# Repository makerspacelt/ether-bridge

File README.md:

---

Ether-bridge

NOTE: This is only a prototype now, so things might not work, and everything might change 

This hardware is meant as an Ethernet upgrade for devices that only support
I2C/UART/RS485/CAN communications. This should be used with a device-specific
firmware that exposes SCPI commands for all functions of a particular device.

Basic target features:

* Ethernet connection
* PoE .af 12w
* CAN
* RS-485
* i2c/UART
* 1x GPIO
* LXI/SCPI support via raw TCP
* Compatibility with ESPHome and Home Assistant

Dev NOTE: before commit, run `./kibot.sh` to regenerate documentation, bom, gerbers and other assets.

* [schematics.pdf](gen/schematics.pdf)
* [pcb.pdf with dimensions](gen/pcb.pdf)
* [ibom.html](gen/single/ibom.html)

---

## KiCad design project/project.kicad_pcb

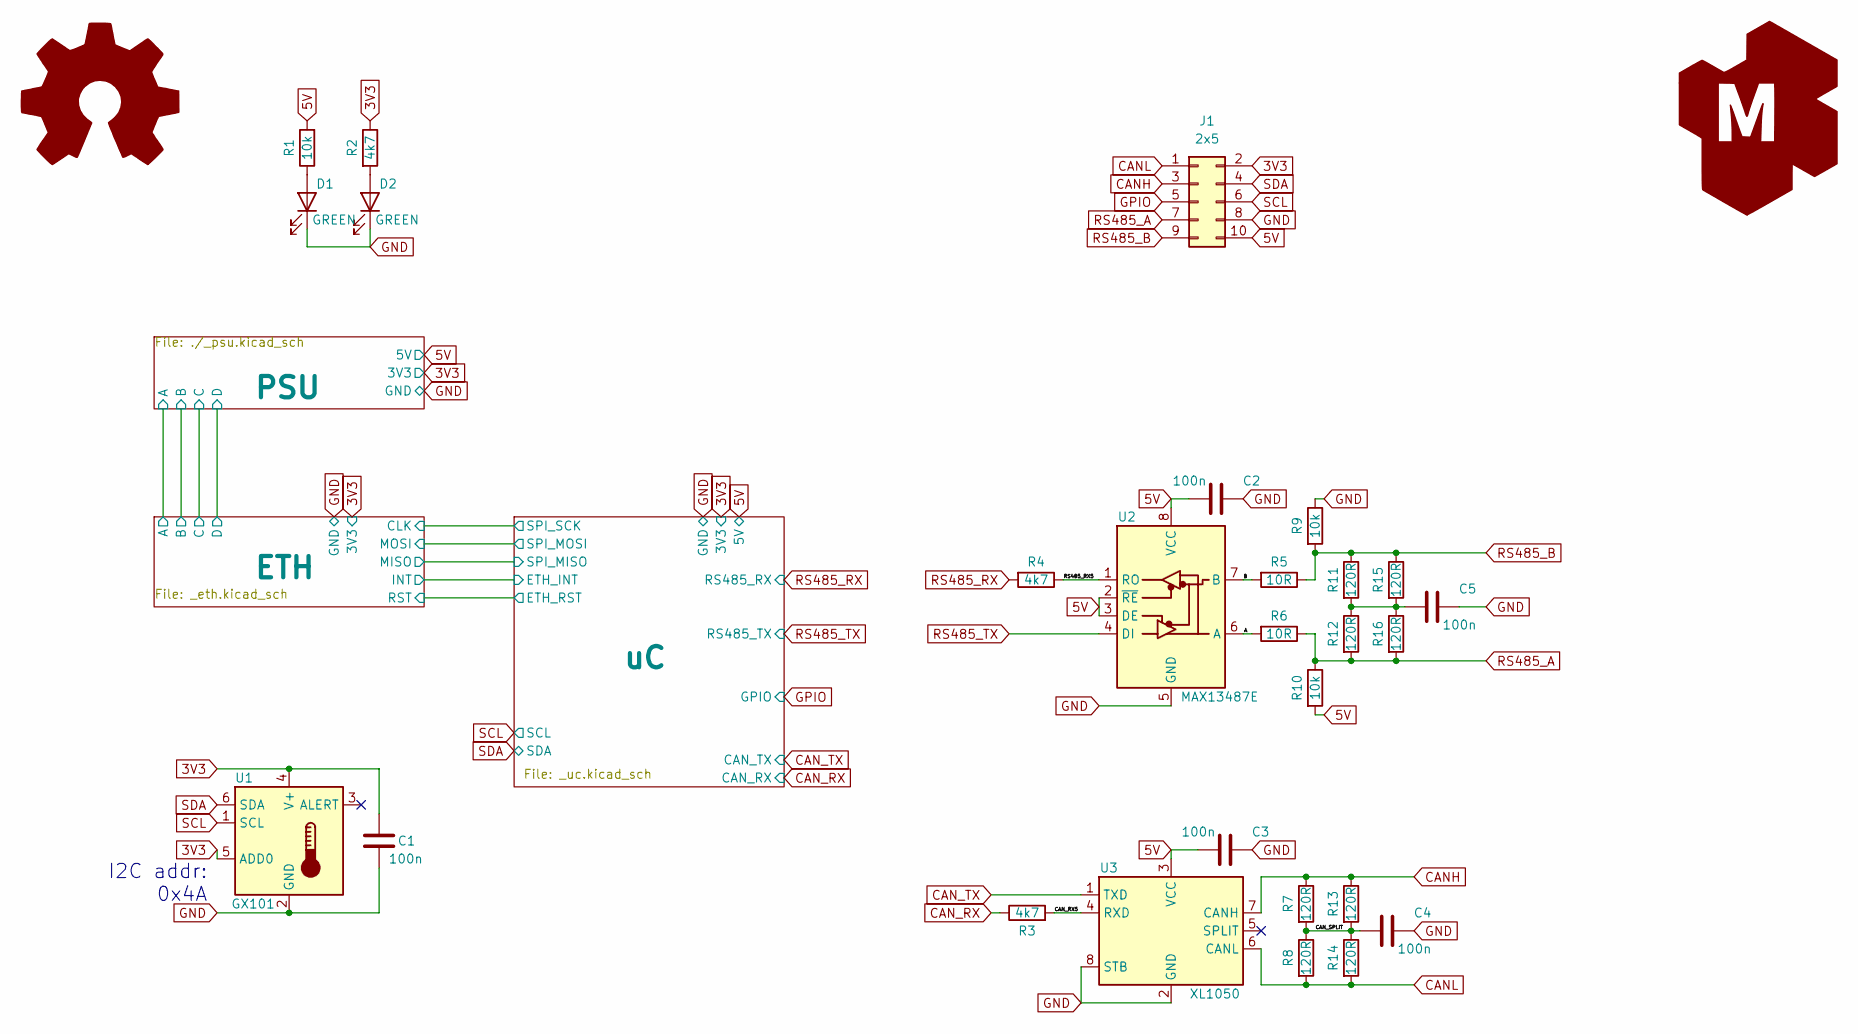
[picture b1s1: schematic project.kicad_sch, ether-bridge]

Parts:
C1, C2, C3, C4, C5: 100n; C_0402_1005Metric_Pad0.74x0.62mm_HandSolder; jlc-part-type B+
D1, D2: GREEN; LED_0805_2012Metric_Pad1.15x1.40mm_HandSolder; jlc-part-type B+
G1: Logo_Open_Hardware_Large; OSHW-Symbol_6.7x6mm_SilkScreen
G2: LOGO_KMS; logo_kms_small_silkscreen
J1: 2x5; PinHeader_2x05_P2.54mm_Vertical
R1, R9, R10: 10k; R_0402_1005Metric_Pad0.72x0.64mm_HandSolder; jlc-part-type B+
R2, R3, R4: 4k7; R_0402_1005Metric_Pad0.72x0.64mm_HandSolder; jlc-part-type B+
R5, R6: 10R; R_0402_1005Metric_Pad0.72x0.64mm_HandSolder; jlc-part-type B+
R7, R8, R11, R12, R13, R14, R15, R16: 120R; R_0402_1005Metric_Pad0.72x0.64mm_HandSolder; jlc-part-type B+
U1: GX101; SOT-23-6; jlc-part-type E+
U2: MAX13487E; SOIC-8_3.9x4.9mm_P1.27mm; jlc-part-type E+
U3: XL1050; SOIC-8_3.9x4.9mm_P1.27mm; jlc-part-type E+

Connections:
3V3: C1.1, J1.2, R2.1, U1.4 (V+), U1.5 (ADD0); also elsewhere on the board
5V: C2.1, C3.1, J1.10, R1.2, R10.2, U2.2 (~RE), U2.3 (DE), U2.8 (VCC), U3.3 (VCC); also elsewhere on the board
/A: R6.2, U2.6 (A)
/B: R5.2, U2.7 (B)
/CAN_RX5: R3.2, U3.4 (RXD)
/CAN_SPLIT: C4.1, R7.2, R8.1, R13.2, R14.1
/RS485_RX5: R4.1, U2.1 (RO)
CANH: J1.3, R7.1, R13.1, U3.7 (CANH)
CANL: J1.1, R8.2, R14.2, U3.6 (CANL)
CAN_RX: R3.1; also elsewhere on the board
CAN_TX: U3.1 (TXD); also elsewhere on the board
GND: C1.2, C2.2, C3.2, C4.2, C5.2, D1.1 (K), D2.1 (K), J1.8, R9.1, U1.2 (GND), U2.5 (GND), U3.2 (GND), U3.8 (STB); also elsewhere on the board
GPIO: J1.5; also elsewhere on the board
unnamed: C5.1, R11.2, R12.1, R15.2, R16.1
unnamed: D1.2 (A), R1.1
unnamed: D2.2 (A), R2.2
RS485_A: J1.7, R6.1, R10.1, R12.2, R16.2
RS485_B: J1.9, R5.1, R9.2, R11.1, R15.1
RS485_RX: R4.2; also elsewhere on the board
RS485_TX: U2.4 (DI); also elsewhere on the board
SCL: J1.6, U1.1 (SCL); also elsewhere on the board
SDA: J1.4, U1.6 (SDA); also elsewhere on the board

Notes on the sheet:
I2C addr: 0x4A

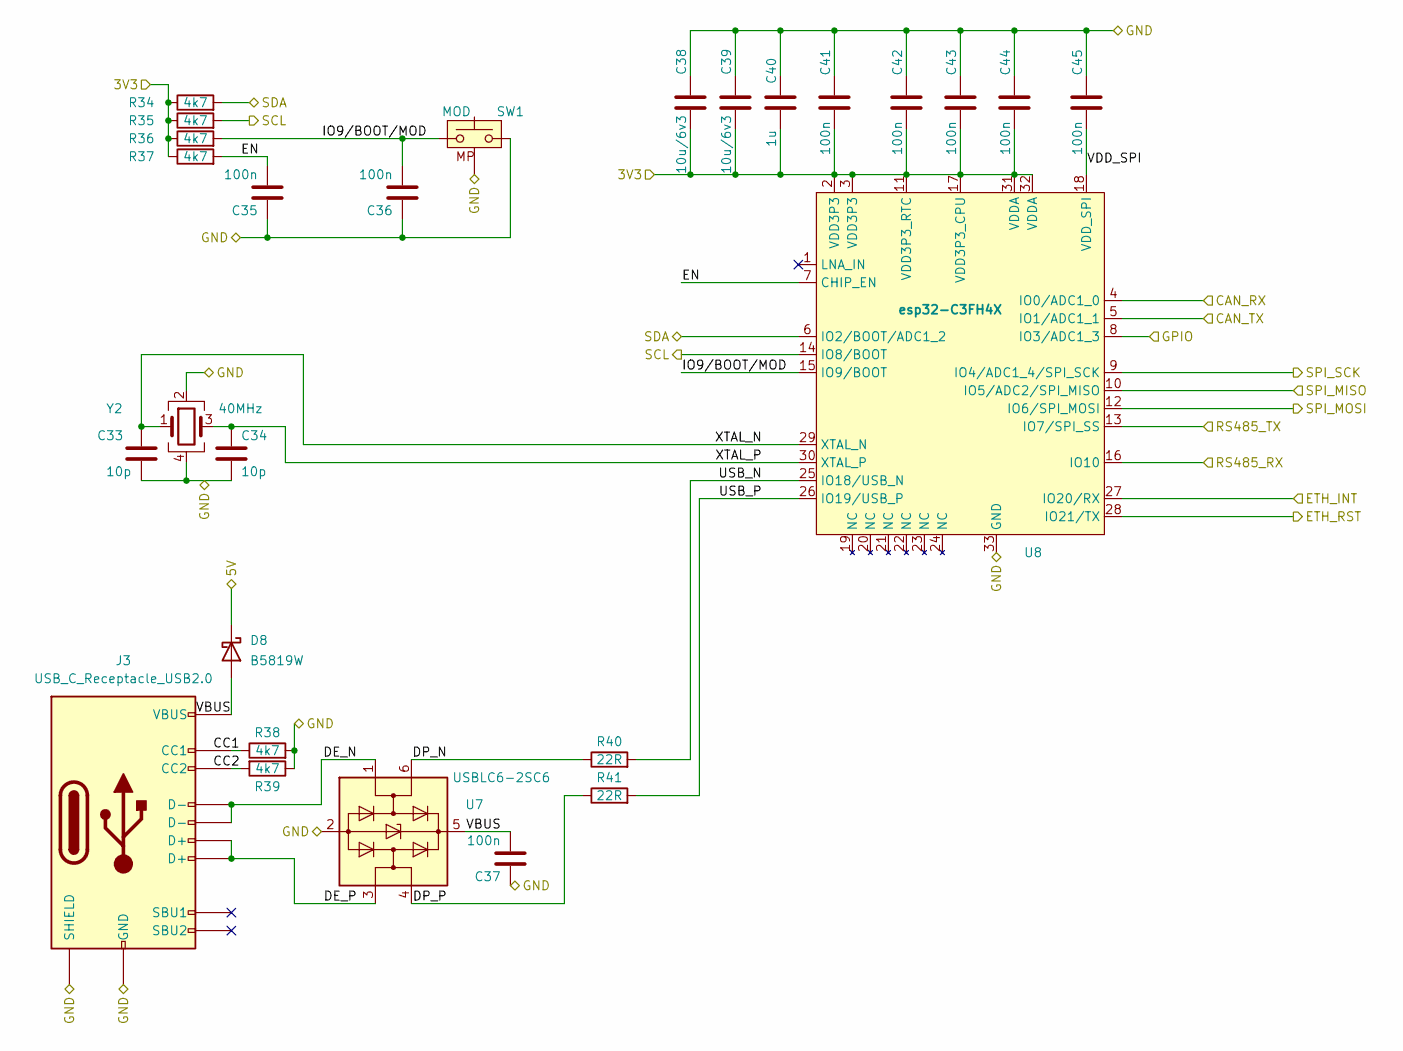
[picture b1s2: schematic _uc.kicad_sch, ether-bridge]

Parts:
C33, C34: 10p; C_0402_1005Metric; jlc-part-type ???
C35, C36, C37, C41, C42, C43, C44, C45: 100n; C_0402_1005Metric_Pad0.74x0.62mm_HandSolder; jlc-part-type B+
C38, C39: 10u/6v3; C_0402_1005Metric_Pad0.74x0.62mm_HandSolder; jlc-part-type B+
C40: 1u; C_0402_1005Metric_Pad0.74x0.62mm_HandSolder; jlc-part-type B+
D8: B5819W; D_SOD-123; jlc-part-type B+
J3: USB_C_Receptacle_USB2.0; USB_C_Receptacle_HRO_TYPE-C-31-M-12; jlc-part-type E+
R34, R35, R36, R37, R38, R39: 4k7; R_0402_1005Metric_Pad0.72x0.64mm_HandSolder; jlc-part-type B+
R40, R41: 22R; R_0402_1005Metric_Pad0.72x0.64mm_HandSolder; jlc-part-type B+
SW1: MOD; tiny-btn; jlc-part-type E+
U7: USBLC6-2SC6; SOT-23-6; jlc-part-type E+
U8: esp32-C3FH4X; QFN-32-1EP_5x5mm_P0.5mm_EP3.65x3.65mm; jlc-part-type E+
Y2: 40MHz; Crystal_SMD_2016-4Pin_2.0x1.6mm; jlc-part-type E+

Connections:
3V3: C38.2, C39.2, C40.2, C41.1, C42.1, C43.1, C44.1, R34.1, R35.1, R36.1, R37.1, U8.2 (VDD3P3), U8.3 (VDD3P3), U8.11 (VDD3P3_RTC), U8.17 (VDD3P3_CPU), U8.31 (VDDA), U8.32 (VDDA); also elsewhere on the board
5V: D8.1 (K); also elsewhere on the board
/ETH/CLK: U8.9 (IO4/ADC1_4/SPI_SCK); also elsewhere on the board
/ETH/INT: U8.27 (IO20/RX); also elsewhere on the board
/ETH/MISO: U8.10 (IO5/ADC2/SPI_MISO); also elsewhere on the board
/ETH/MOSI: U8.12 (IO6/SPI_MOSI); also elsewhere on the board
/ETH/RST: U8.28 (IO21/TX); also elsewhere on the board
/uC/CC1: J3.A5 (CC1), R38.1
/uC/CC2: J3.B5 (CC2), R39.2
/uC/DE_N: J3.A7 (D-), J3.B7 (D-), U7.1 (I/O1)
/uC/DE_P: J3.A6 (D+), J3.B6 (D+), U7.3 (I/O2)
/uC/DP_N: R40.1, U7.6 (I/O1)
/uC/DP_P: R41.1, U7.4 (I/O2)
/uC/EN: C35.2, R37.2, U8.7 (CHIP_EN)
/uC/IO9/BOOT/MOD: C36.2, R36.2, SW1.2, U8.15 (IO9/BOOT)
/uC/USB_N: R40.2, U8.25 (IO18/USB_N)
/uC/USB_P: R41.2, U8.26 (IO19/USB_P)
/uC/VBUS: C37.2, D8.2 (A), J3.A4 (VBUS), J3.A9 (VBUS), J3.B4 (VBUS), J3.B9 (VBUS), U7.5 (VBUS)
/uC/VDD_SPI: C45.1, U8.18 (VDD_SPI)
/uC/XTAL_N: C33.1, U8.29 (XTAL_N), Y2.1
/uC/XTAL_P: C34.1, U8.30 (XTAL_P), Y2.3
CAN_RX: U8.4 (IO0/ADC1_0); also elsewhere on the board
CAN_TX: U8.5 (IO1/ADC1_1); also elsewhere on the board
GND: C33.2, C34.2, C35.1, C36.1, C37.1, C38.1, C39.1, C40.1, C41.2, C42.2, C43.2, C44.2, C45.2, J3.A1 (GND), J3.A12 (GND), J3.B1 (GND), J3.B12 (GND), J3.S1 (SHIELD), R38.2, R39.1, SW1.1, SW1.MP, U7.2 (GND), U8.33 (GND), Y2.2, Y2.4; also elsewhere on the board
GPIO: U8.8 (IO3/ADC1_3); also elsewhere on the board
RS485_RX: U8.16 (IO10); also elsewhere on the board
RS485_TX: U8.13 (IO7/SPI_SS); also elsewhere on the board
SCL: R35.2, U8.14 (IO8/BOOT); also elsewhere on the board
SDA: R34.2, U8.6 (IO2/BOOT/ADC1_2); also elsewhere on the board

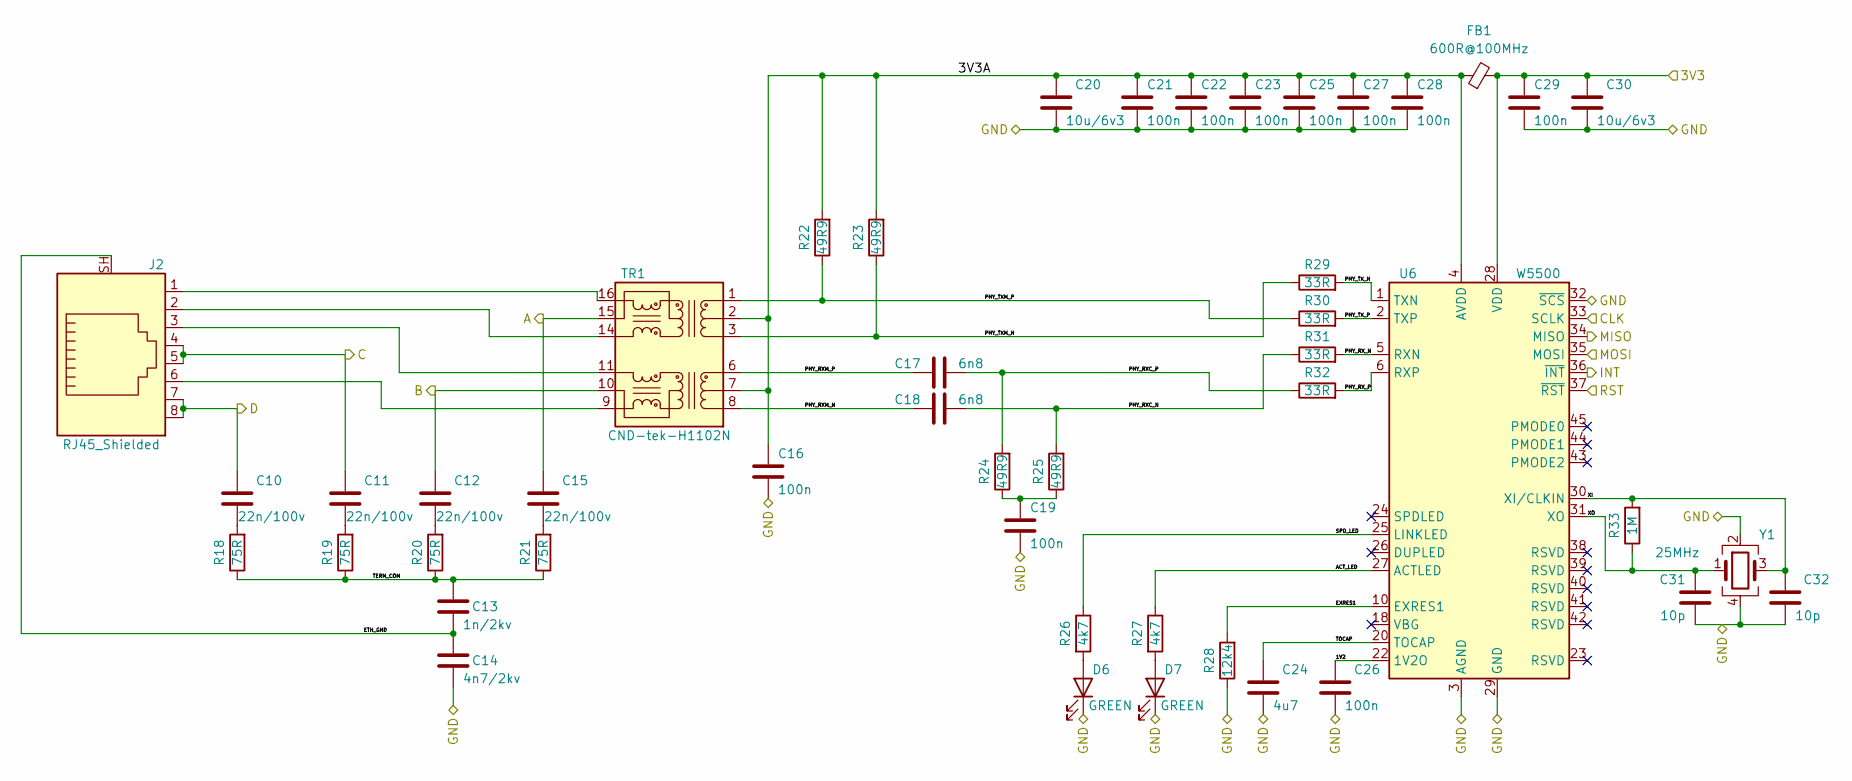
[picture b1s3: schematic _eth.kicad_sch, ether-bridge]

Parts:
C10, C11, C12, C15: 22n/100v; C_0603_1608Metric_Pad1.08x0.95mm_HandSolder; jlc-part-type E+
C13: 1n/2kv; C_1206_3216Metric_Pad1.33x1.80mm_HandSolder; jlc-part-type B+
C14: 4n7/2kv; C_1206_3216Metric_Pad1.33x1.80mm_HandSolder; jlc-part-type E+
C16, C19, C21, C22, C23, C25, C26, C27, C28, C29: 100n; C_0402_1005Metric_Pad0.74x0.62mm_HandSolder; jlc-part-type B+
C17, C18: 6n8; C_0603_1608Metric_Pad1.08x0.95mm_HandSolder; jlc-part-type B+
C20, C30: 10u/6v3; C_0402_1005Metric_Pad0.74x0.62mm_HandSolder; jlc-part-type B+
C24: 4u7; C_0402_1005Metric_Pad0.74x0.62mm_HandSolder; jlc-part-type B+
C31, C32: 10p; C_0402_1005Metric; jlc-part-type ???
D6, D7: GREEN; LED_0402_1005Metric_Pad0.77x0.64mm_HandSolder; jlc-part-type E+
FB1: 600R@100MHz; L_0805_2012Metric_Pad1.05x1.20mm_HandSolder; jlc-part-type B+
J2: RJ45_Shielded; RJ45_FG_RJ-064-1; jlc-part-type E+
R18, R19, R20, R21: 75R; R_0402_1005Metric_Pad0.72x0.64mm_HandSolder; jlc-part-type ER+
R22, R23, R24, R25: 49R9; R_0402_1005Metric_Pad0.72x0.64mm_HandSolder; jlc-part-type B+
R26, R27: 4k7; R_0402_1005Metric_Pad0.72x0.64mm_HandSolder; jlc-part-type B+
R28: 12k4; R_0402_1005Metric_Pad0.72x0.64mm_HandSolder; jlc-part-type E+
R29, R30, R31, R32: 33R; R_0402_1005Metric_Pad0.72x0.64mm_HandSolder; jlc-part-type B+
R33: 1M; R_0402_1005Metric_Pad0.72x0.64mm_HandSolder; jlc-part-type B+
TR1: CND-tek-H1102N; Transformer_Ethernet_SO-16_7.11x12.7mm; jlc-part-type E+
U6: W5500; LQFP-48_7x7mm_P0.5mm; jlc-part-type E+
Y1: 25MHz; Crystal_SMD_2016-4Pin_2.0x1.6mm; jlc-part-type E+

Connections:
3V3: C29.1, C30.1, FB1.2, U6.28 (VDD); also elsewhere on the board
/ETH/1V2: C26.1, U6.22 (1V2O)
/ETH/3V3A: C16.1, C20.1, C21.1, C22.1, C23.1, C25.1, C27.1, C28.1, FB1.1, R22.2, R23.2, TR1.2 (C_TD), TR1.7 (C_RD), U6.4 (AVDD), U6.8 (AVDD), U6.11 (AVDD), U6.15 (AVDD), U6.17 (AVDD), U6.21 (AVDD)
/ETH/A: C15.1, TR1.15 (C_TX); also elsewhere on the board
/ETH/ACT_LED: R27.1, U6.27 (ACTLED)
/ETH/B: C12.1, TR1.10 (C_RX); also elsewhere on the board
/ETH/C: C11.1, J2.4, J2.5; also elsewhere on the board
/ETH/CLK: U6.33 (SCLK); also elsewhere on the board
/ETH/D: C10.1, J2.7, J2.8; also elsewhere on the board
/ETH/ETH_GND: C13.2, C14.1, J2.SH
/ETH/EXRES1: R28.2, U6.10 (EXRES1)
/ETH/INT: U6.36 (~INT); also elsewhere on the board
/ETH/MISO: U6.34 (MISO); also elsewhere on the board
/ETH/MOSI: U6.35 (MOSI); also elsewhere on the board
/ETH/PHY_RXC_N: C18.2, R25.2, R31.1
/ETH/PHY_RXC_P: C17.2, R24.2, R32.1
/ETH/PHY_RXM_N: C18.1, TR1.8 (RD-)
/ETH/PHY_RXM_P: C17.1, TR1.6 (RD+)
/ETH/PHY_RX_N: R31.2, U6.5 (RXN)
/ETH/PHY_RX_P: R32.2, U6.6 (RXP)
/ETH/PHY_TXM_N: R23.1, R29.1, TR1.3 (TD-)
/ETH/PHY_TXM_P: R22.1, R30.1, TR1.1 (TD+)
/ETH/PHY_TX_N: R29.2, U6.1 (TXN)
/ETH/PHY_TX_P: R30.2, U6.2 (TXP)
/ETH/RST: U6.37 (~RST); also elsewhere on the board
/ETH/SPD_LED: R26.1, U6.25 (LINKLED)
/ETH/TERM_COM: C13.1, R18.1, R19.1, R20.1, R21.1
/ETH/TOCAP: C24.1, U6.20 (TOCAP)
/ETH/XI: C32.1, R33.2, U6.30 (XI/CLKIN), Y1.3
/ETH/XO: C31.1, R33.1, U6.31 (XO), Y1.1
GND: C14.2, C16.2, C19.2, C20.2, C21.2, C22.2, C23.2, C24.2, C25.2, C26.2, C27.2, C28.2, C29.2, C30.2, C31.2, C32.2, D6.1 (K), D7.1 (K), R28.1, U6.3 (AGND), U6.9 (AGND), U6.14 (AGND), U6.16 (AGND), U6.19 (AGND), U6.29 (GND), U6.32 (~SCS), U6.48 (AGND), Y1.2, Y1.4; also elsewhere on the board
unnamed: C10.2, R18.2
unnamed: C11.2, R19.2
unnamed: C12.2, R20.2
unnamed: C15.2, R21.2
unnamed: C19.1, R24.1, R25.1
unnamed: D6.2 (A), R26.2
unnamed: D7.2 (A), R27.2
unnamed: J2.1, TR1.16 (TX+)
unnamed: J2.2, TR1.14 (TX-)
unnamed: J2.3, TR1.11 (RX+)
unnamed: J2.6, TR1.9 (RX-)

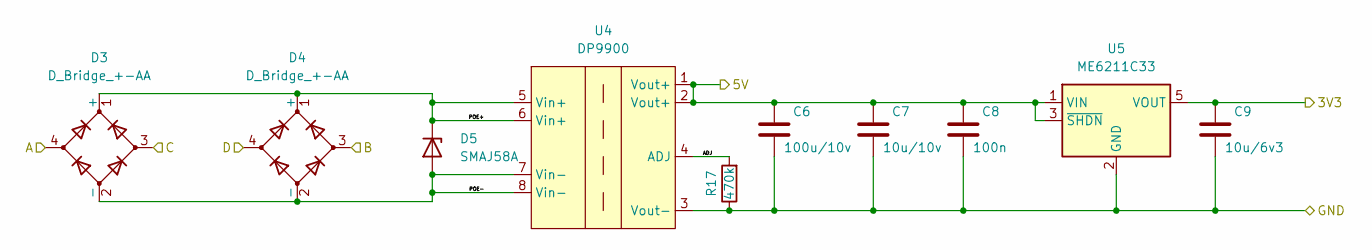
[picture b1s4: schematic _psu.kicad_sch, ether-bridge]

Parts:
C6: 100u/10v; C_1206_3216Metric_Pad1.33x1.80mm_HandSolder; jlc-part-type E+
C7: 10u/10v; C_0603_1608Metric_Pad1.08x0.95mm_HandSolder; jlc-part-type B+
C8: 100n; C_0402_1005Metric_Pad0.74x0.62mm_HandSolder; jlc-part-type B+
C9: 10u/6v3; C_0402_1005Metric_Pad0.74x0.62mm_HandSolder; jlc-part-type B+
D3, D4: D_Bridge_+-AA; Diode_Bridge_Diotec_MicroDil_3.0x3.0x1.8mm; jlc-part-type E+
D5: SMAJ58A; D_SMA; jlc-part-type E+
R17: 470k; R_0402_1005Metric_Pad0.72x0.64mm_HandSolder; jlc-part-type ER+
U4: DP9900; PSU_DP9900LP; jlc-part-type E+
U5: ME6211C33; SOT-23-5; jlc-part-type E+

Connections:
3V3: C9.1, U5.5 (VOUT); also elsewhere on the board
5V: C6.1, C7.1, C8.1, U4.1 (Vout+), U4.2 (Vout+), U5.1 (VIN), U5.3 (~SHDN); also elsewhere on the board
/ETH/A: D3.4; also elsewhere on the board
/ETH/B: D4.3; also elsewhere on the board
/ETH/C: D3.3; also elsewhere on the board
/ETH/D: D4.4; also elsewhere on the board
/PSU/ADJ: R17.2, U4.4 (ADJ)
/PSU/POE+: D3.1 (+), D4.1 (+), D5.1 (K), U4.5 (Vin+), U4.6 (Vin+)
/PSU/POE-: D3.2 (-), D4.2 (-), D5.2 (A), U4.7 (Vin-), U4.8 (Vin-)
GND: C6.2, C7.2, C8.2, C9.2, R17.1, U4.3 (Vout-), U5.2 (GND); also elsewhere on the board

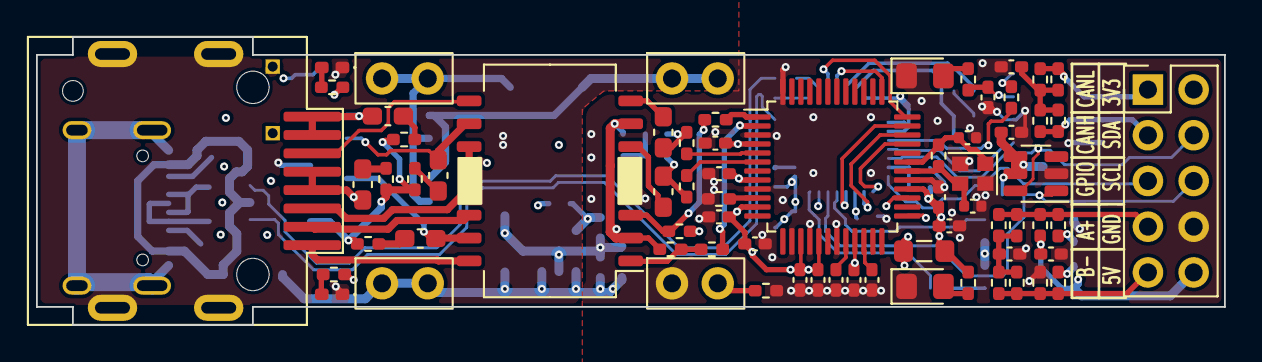
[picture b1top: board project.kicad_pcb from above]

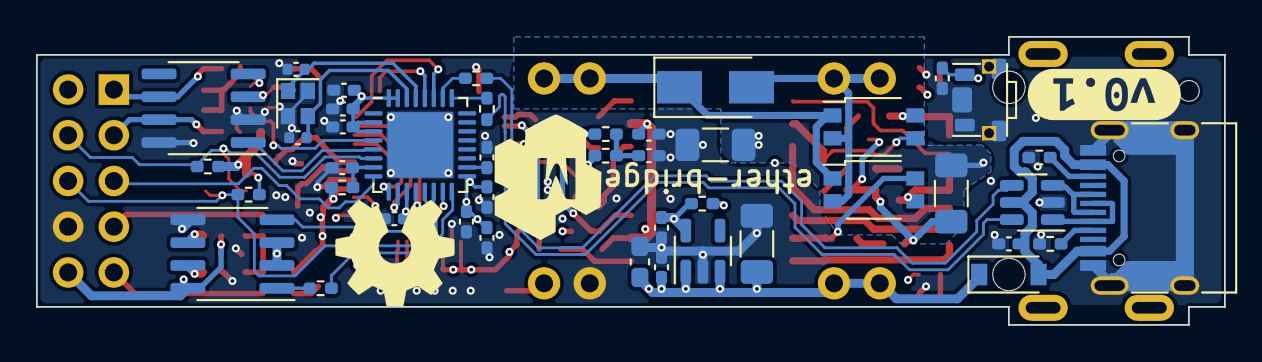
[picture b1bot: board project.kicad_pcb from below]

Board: 6 copper layers, 66.0 x 16.0 mm, 113 parts (47 on the bottom side), 79 nets.

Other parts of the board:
kibuzzard-6862F65F: G***; kibuzzard-6862F65F

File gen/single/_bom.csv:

"Row","Description","Part","References","Value","Footprint","Quantity Per PCB","Status","Datasheet","jlc-part-type","lcsc#"
"1","Unpolarized capacitor","C","C31,C32,C33,C34","10p","C_0402_1005Metric","4"," ","~","???","C1634"
"2","Unpolarized capacitor","C","C17,C18","6n8","C_0603_1608Metric_Pad1.08x0.95mm_HandSolder","2"," ","~","B+","C1631"
"3","Unpolarized capacitor","C","C1,C2,C3,C4,C5,C8,C16,C19,C21,C22,C23,C25,C26,C27,C28,C29,C35,C36,C37,C41,C42,C43,C44,C45","100n","C_0402_1005Metric_Pad0.74x0.62mm_HandSolder","24"," ","~","B+","C1525"
"4","Unpolarized capacitor","C","C40","1u","C_0402_1005Metric_Pad0.74x0.62mm_HandSolder","1"," ","~","B+","C52923"
"5","Unpolarized capacitor","C","C24","4u7","C_0402_1005Metric_Pad0.74x0.62mm_HandSolder","1"," ","~","B+","C23733"
"6","Unpolarized capacitor","C","C6","100u/10v","C_1206_3216Metric_Pad1.33x1.80mm_HandSolder","1"," ","~","E+","C312983"
"7","Unpolarized capacitor","C","C7","10u/10v","C_0603_1608Metric_Pad1.08x0.95mm_HandSolder","1"," ","~","B+","C19702"
"8","Unpolarized capacitor","C","C9,C20,C30,C38,C39","10u/6v3","C_0402_1005Metric_Pad0.74x0.62mm_HandSolder","5"," ","~","B+","C15525"
"9","Unpolarized capacitor","C","C13","1n/2kv","C_1206_3216Metric_Pad1.33x1.80mm_HandSolder","1"," ","~","B+","C9196"
"10","Unpolarized capacitor","C","C10,C11,C12,C15","22n/100v","C_0603_1608Metric_Pad1.08x0.95mm_HandSolder","4"," ","~","E+","C22374871"
"11","Unpolarized capacitor","C","C14","4n7/2kv","C_1206_3216Metric_Pad1.33x1.80mm_HandSolder","1"," ","~","E+","C41017"
"12","Schottky diode","D_Schottky","D8","B5819W","D_SOD-123","1"," ","https://www.lcsc.com/datasheet/lcsc_datasheet_2304140030_Jia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","B+","C8598"
"13","Diode bridge, +ve/-ve/AC/AC","D_Bridge_+-AA","D3,D4","D_Bridge_+-AA","Diode_Bridge_Diotec_MicroDil_3.0x3.0x1.8mm","2"," ","https://lcsc.com/datasheet/lcsc_datasheet_2410122110_-DIOTEC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","E+","C3589227"
"14","Light emitting diode","LED","D1,D2","GREEN","LED_0805_2012Metric_Pad1.15x1.40mm_HandSolder","2"," ","https://lcsc.com/datasheet/lcsc_datasheet_1806151820_Hubei-K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","B+","C2297"
"15","Light emitting diode","LED","D6,D7","GREEN","LED_0402_1005Metric_Pad0.77x0.64mm_HandSolder","2"," ","https://lcsc.com/datasheet/lcsc_datasheet_2504101957_XINGLIG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","E+","C965793"
"16","Zener diode","D_Zener","D5","SMAJ58A","D_SMA","1"," ","https://lcsc.com/datasheet/lcsc_datasheet_2504211430_GOODWOR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","E+","C2980408"
"17","Ferrite bead, small symbol","FerriteBead_Small","FB1","600R@100MHz","L_0805_2012Metric_Pad1.05x1.20mm_HandSolder","1"," ","~","B+","C1017"
"18","Generic connector, double row, 02x05, odd/even pin numbering scheme (row 1 odd numbers, row 2 even numbers), script generated (kicad-library-utils/schlib/autogen/connector/)","Conn_02x05_Odd_Even","J1","2x5","PinHeader_2x05_P2.54mm_Vertical","1"," ","~","-",""
"19","RJ connector, 8P8C (8 positions 8 connected), Shielded","RJ45_Shielded","J2","RJ45_Shielded","RJ45_FG_RJ-064-1","1"," ","https://lcsc.com/datasheet/lcsc_datasheet_2306211558_FG-RJ-0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","E+","C7205199"
"20","USB 2.0-only Type-C Receptacle connector","USB_C_Receptacle_USB2.0","J3","USB_C_Receptacle_USB2.0","USB_C_Receptacle_HRO_TYPE-C-31-M-12","1"," ","https://lcsc.com/datasheet/lcsc_datasheet_2410010003_Korean-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","E+","C165948"
"21","Resistor","R","R5,R6","10R","R_0402_1005Metric_Pad0.72x0.64mm_HandSolder","2"," ","~","B+","C25077"
"22","Resistor","R","R40,R41","22R","R_0402_1005Metric_Pad0.72x0.64mm_HandSolder","2"," ","~","B+","C25092"
"23","Resistor","R","R29,R30,R31,R32","33R","R_0402_1005Metric_Pad0.72x0.64mm_HandSolder","4"," ","~","B+","C25105"
"24","Resistor","R","R22,R23,R24,R25","49R9","R_0402_1005Metric_Pad0.72x0.64mm_HandSolder","4"," ","~","B+","C25120"
"25","Resistor","R","R18,R19,R20,R21","75R","R_0402_1005Metric_Pad0.72x0.64mm_HandSolder","4"," ","~","ER+","C25133"
"26","Resistor","R","R7,R8,R11,R12,R13,R14,R15,R16","120R","R_0402_1005Metric_Pad0.72x0.64mm_HandSolder","8"," ","~","B+","C25079"
"27","Resistor","R","R2,R3,R4,R26,R27,R34,R35,R36,R37,R38,R39","4k7","R_0402_1005Metric_Pad0.72x0.64mm_HandSolder","11"," ","~","B+","C25900"
"28","Resistor","R","R1,R9,R10","10k","R_0402_1005Metric_Pad0.72x0.64mm_HandSolder","3"," ","~","B+","C25744"
"29","Resistor","R","R28","12k4","R_0402_1005Metric_Pad0.72x0.64mm_HandSolder","1"," ","~","E+","C11692"
"30","Resistor","R","R17","470k","R_0402_1005Metric_Pad0.72x0.64mm_HandSolder","1"," ","~","ER+","C25790"
"31","Resistor","R","R33","1M","R_0402_1005Metric_Pad0.72x0.64mm_HandSolder","1"," ","~","B+","C26083"
"32","Push button switch, generic, two pins","SW_Push_MountingPin","SW1","MOD","tiny-btn","1"," ","https://lcsc.com/datasheet/lcsc_datasheet_2410121643_ALPSALP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","E+","C380198"
"33","Ethernet LAN 10/100 Base-Tx Transformer CT, SMD","Wuerth_749013011A","TR1","CND-tek-H1102N","Transformer_Ethernet_SO-16_7.11x12.7mm","1"," ","https://lcsc.com/datasheet/lcsc_datasheet_2412231915_CND-tek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","E+","C42418465"
"34","","DP9900","U4","DP9900","PSU_DP9900LP","1"," ","https://lcsc.com/datasheet/lcsc_datasheet_2410122022_SDAPO-D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","E+","C5380108"
"35","Digital Temperature Sensor with I2C/SMBus Interface, +/-2° C, one-shot conversion, alert, SOT-23-6","TMP101","U1","GX101","SOT-23-6","1"," ","https://www.lcsc.com/datasheet/lcsc_datasheet_2409280202_GXC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","E+","C5441728"
"36","Half duplex RS-485/RS-422, 0.25 Mbps, ±15kV electro-static discharge (ESD) protection, with slew-rate, with low-power shutdown, with receiver/driver enable, 128 receiver drive kapacitity, DIP-8 and SOIC-8","MAX487E","U2","MAX13487E","SOIC-8_3.9x4.9mm_P1.27mm","1"," ","https://lcsc.com/datasheet/lcsc_datasheet_2410121837_Analog-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","E+","C18347"
"37","150mA, Tiny CMOS LDO With Shutdown, Fixed Voltage, SOT-23-5","MCP1802x-xx02xOT","U5","ME6211C33","SOT-23-5","1"," ","https://lcsc.com/datasheet/lcsc_datasheet_1811131510_MICRONE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","E+","C82942"
"38","Very low capacitance ESD protection diode, 2 data-line, SOT-23-6","USBLC6-2SC6","U7","USBLC6-2SC6","SOT-23-6","1"," ","https://www.lcsc.com/datasheet/lcsc_datasheet_2311091738_UMW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","E+","C2687116"
"39","10/100Mb SPI Ethernet controller with TCP/IP stack, LQFP-48","W5500","U6","W5500","LQFP-48_7x7mm_P0.5mm","1"," ","https://lcsc.com/datasheet/lcsc_datasheet_2410121618_WIZNET-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","E+","C32843"
"40","High-Speed CAN Transceiver, standby mode, split pin, SOIC-8","TJA1042T","U3","XL1050","SOIC-8_3.9x4.9mm_P1.27mm","1"," ","https://www.lcsc.com/datasheet/lcsc_datasheet_2309141025_XIN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","E+","C609746"
"41","esp32-C3FH4X 4MB flash QFN32-1EP 5x5mm EP3.7x3.7mm","esp32-C3FH4X","U8","esp32-C3FH4X","QFN-32-1EP_5x5mm_P0.5mm_EP3.65x3.65mm","1"," ","https://www.espressif.com/sites/default/files/documentation/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","E+","C2858491"
"42","Four pin crystal, GND on pins 2 and 4","Crystal_GND24","Y1","25MHz","Crystal_SMD_2016-4Pin_2.0x1.6mm","1"," ","https://lcsc.com/datasheet/lcsc_datasheet_2504101957_Shenzhe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","E+","C7301943"
"43","Four pin crystal, GND on pins 2 and 4","Crystal_GND24","Y2","40MHz","Crystal_SMD_2016-4Pin_2.0x1.6mm","1"," ","https://lcsc.com/datasheet/lcsc_datasheet_2409272203_Yajingx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","E+","C20885029"

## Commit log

2025-07-02 v0.1
2025-08-25 enlarging vias to 0.45mm
